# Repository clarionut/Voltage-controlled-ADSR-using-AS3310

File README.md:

# Voltage controlled ADSR using AS3310

This repository contains details of my modified version of the [Digisound 80-18 multifunction envelope generator]( http://www.digisound80.co.uk/digisound/modules/80-18.htm). I was particularly interested in its versatility with three operating modes
- normal (standard ADSR)
- automatic (gives a complete ADR cycle following a brief trigger input)
- damped (gives a piano-like envelope with initial attack and decay, but instead of a constant sustain while the gate is high the envelope continues to decay at a rate determined by the release setting, finally shutting off the envelope when the gate goes low)

Curiously, given that the 3310 chip is intrinsically voltage controlled, the Digisound 80-18 module only featured control of the envelope by potentiometers rather than allowing external CV control, although there are other designs (e.g. by [gerb-ster](https://github.com/gerb-ster/Curtis-VC-ADSR)) which do allow external control.

I'm absolutely delighted with this module and immediately built a second. I wouldn't want to be limited to a conventional ADSR having used this one.

## Issues
There is a known issue with the Digisound 80-18 module leading to repeated AD triggering with relatively weak gate inputs. The Digisound 80-18A documentation suggests using two gates from a CD40106 in series to condition the gate signal and [Eddy Bergman used a switch](https://www.eddybergman.com/2020/05/synthesizer-build-part-33-digisound-80.html) to break the loop responsible for multiple triggering. I chose to feed the gate input into an op-amp comparator so even rather low-level gates trigger the ADSR reliably.

Note that I have not encountered any of the odd behaviour in Automatic mode as described by Eddy Bergman, in my case this mode works exactly as described in the Digisound 80-18 documentation.

Running the circuit on a breadboard showed that with linear potentiometers much of the travel of the pot covered only very short time intervals, making the more useful longer times quite hard to adjust. This was easy to fix using fake C-taper pots (500k linear pot with a 100k resistor from the wiper to the +ve supply end of the pot).

## Additional features
I found that in Damped mode the final release was very rapid producing an audible click. Adding a 510R resistor between the AS3310 chip pin 13 and transistor TR2 (Digisound schematic) / Q2 (my schematic) gave a rapid release without clicking. In the end I added a 2k 'Release 2' pot to make this final release phase manually adjustable.

Coincidentally, at the time I was working on this circuit I was also fixing an issue with the envelope generator of the filter in my Formanta Polivoks. This has an autorepeat mode, enabled by setting the envelope to AD mode and the sustain level to zero. It uses an op-amp comparator to generate an internal trigger signal when the envelope voltage falls below a threshold of a few mV. I included this feature in this ADSR, providing an 'end of envelope' output to trigger other events in the synth, and included a LOOP option on the mode switch allowing the module to run continously (essentially as an 'ADR LFO') in Automatic mode with frequencies up to about 120Hz.

The decay CV input is normalled to the attack input and the release input is normalled to decay, allowing flexibility in external CV control.

There are out-of-range monitor LEDs on the four CV inputs to warn if the combined potentiometer & external CV levels exceed the maximum useful control voltage (no damage would result, it simply wouldn't be effective).

## Repository contents
The schematics folder contains the full schematic as a PDF document, the PCB layout (with the front ground plane removed for clarity) and a subfolder containing the kicad 7 project. The kicad schematic and PCB use some custom symbols and footprints so you may have to download my custom [kiCad libraries](https://github.com/clarionut/kiCad_libraries). Note that the PCB layout is intended to be processed by the 'round tracks' kicad plugin as shown in the PCB.pdf document. The kicad project files only include the unprocessed .kicad_pcb file. I've also included the Gerbers (in the Gerbers folder!) of the rounded tracks PCB for direct fabrication in case they're useful for anyone.

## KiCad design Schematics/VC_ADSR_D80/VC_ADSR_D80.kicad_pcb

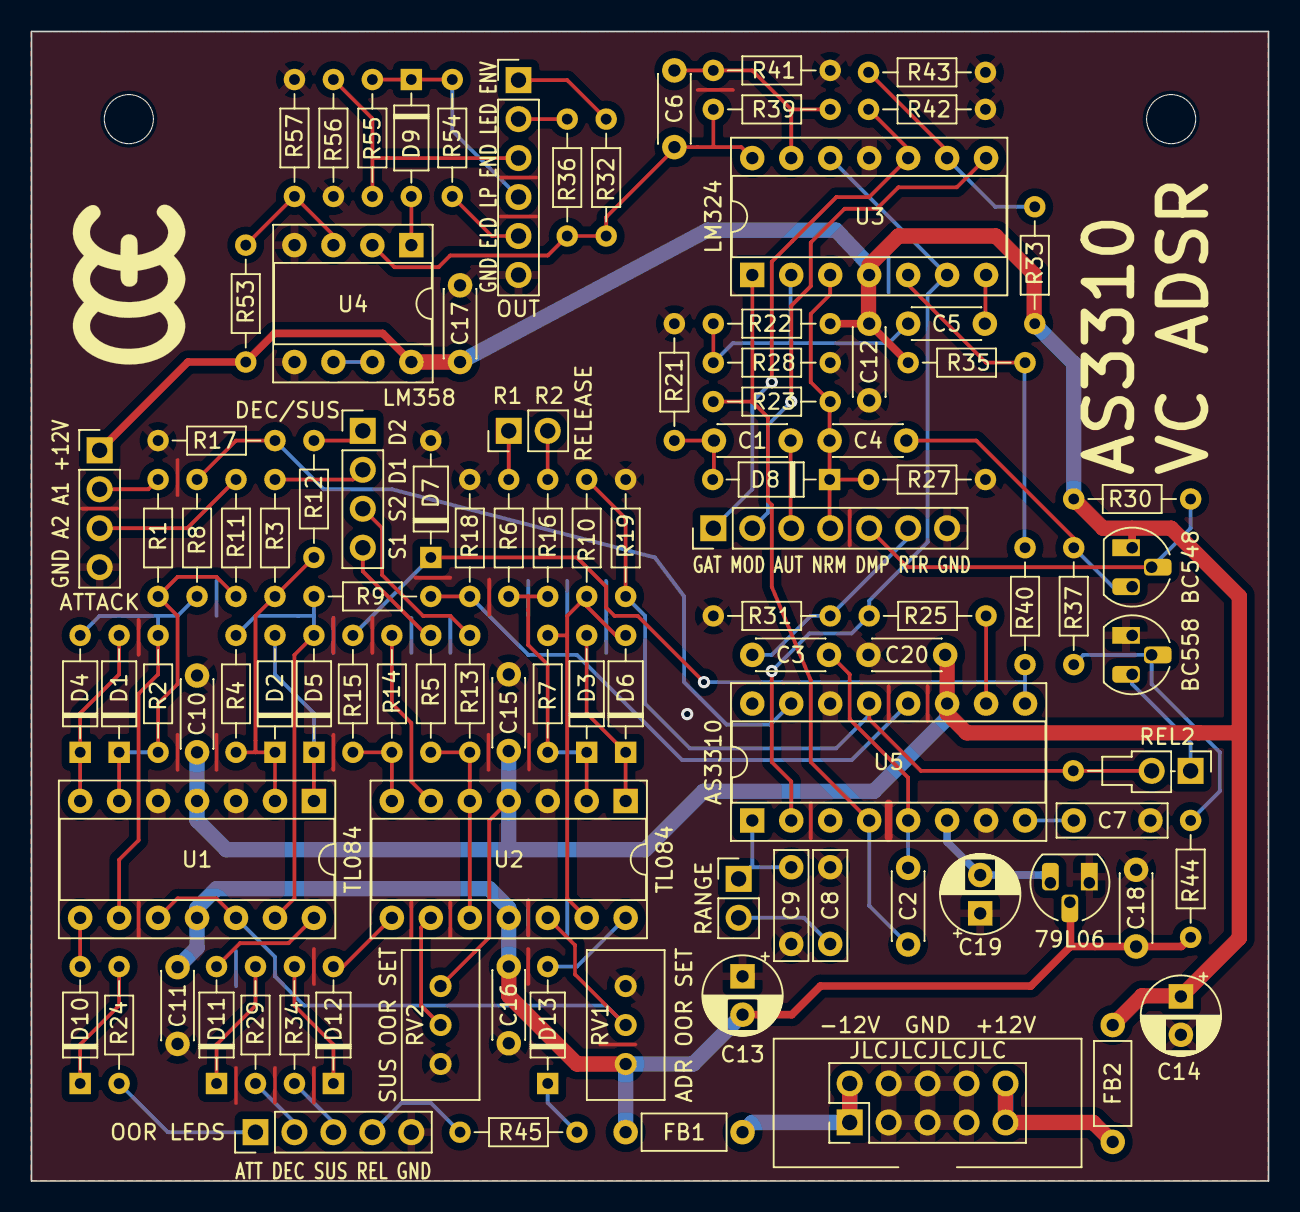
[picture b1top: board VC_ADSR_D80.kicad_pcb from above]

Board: 2 copper layers, 80.6 x 74.9 mm, 101 parts (0 on the bottom side), 75 nets.

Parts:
C1, C5: 33n; C_Disc_D4.3mm_W1.9mm_P5.00mm
C2: 3n3; C_Disc_D4.3mm_W1.9mm_P5.00mm
C3, C4: 10n; C_Disc_D4.3mm_W1.9mm_P5.00mm
C6: 22p; C_Disc_D4.3mm_W1.9mm_P5.00mm
C7: 4n7; C_Rect_L7.0mm_W2.0mm_P5.00mm
C8: 100n; C_Rect_L7.0mm_W2.0mm_P5.00mm
C9: 33n; C_Rect_L7.0mm_W2.0mm_P5.00mm
C10, C11, C12, C15, C16, C17, C20: 100n; C_Disc_D4.3mm_W1.9mm_P5.00mm
C13, C14: 10u; CP_Radial_D5.0mm_P2.50mm
C18: 330n; C_Disc_D4.3mm_W1.9mm_P5.00mm
C19: 1u; CP_Radial_D5.0mm_P2.50mm
D1, D2, D3, D4, D5, D6, D9, D10, D11, D12, D13: 1N914; D_DO-35_SOD27_P7.62mm_Horizontal
D7: 5V1; D_DO-35_SOD27_P7.62mm_Horizontal
D8: BAT43; D_DO-35_SOD27_P7.62mm_Horizontal
FB1, FB2: FB; L_Axial_L5.3mm_D2.2mm_P7.62mm_Horizontal_Vishay_IM-1
J1: ATTACK; PinHeader_1x04_P2.54mm_Vertical
J2: DECAY/SUSTAIN; PinHeader_1x04_P2.54mm_Vertical
J3: RELEASE; PinHeader_1x02_P2.54mm_Vertical
J4: GATE/TRG; PinHeader_1x07_P2.54mm_Vertical
J5: OOR_LEDS; PinHeader_1x05_P2.54mm_Vertical
J6: OUT; PinHeader_1x06_P2.54mm_Vertical
J7: REL.2; Resistor_Header
J8: RANGE; PinHeader_1x02_P2.54mm_Vertical
J9: POWER; Power_2x05
Q1: BC548; TO-92_HandSolder
Q2: BC558; TO-92_HandSolder
R1, R3, R5, R6, R11, R12, R13, R14, R16, R22, R30, R31, R33, R39, R41: 100k; R_Axial_DIN0204_L3.6mm_D1.6mm_P7.62mm_Horizontal
R2, R4, R7: 51k; R_Axial_DIN0204_L3.6mm_D1.6mm_P7.62mm_Horizontal
R8, R9, R10, R24, R29, R34, R45: 20k; R_Axial_DIN0204_L3.6mm_D1.6mm_P7.62mm_Horizontal
R15, R56: 39k; R_Axial_DIN0204_L3.6mm_D1.6mm_P7.62mm_Horizontal
R17, R18, R19, R32: 1k; R_Axial_DIN0204_L3.6mm_D1.6mm_P7.62mm_Horizontal
R21, R23, R36, R40, R43, R54: 10k; R_Axial_DIN0204_L3.6mm_D1.6mm_P7.62mm_Horizontal
R25, R28, R55: 22k; R_Axial_DIN0204_L3.6mm_D1.6mm_P7.62mm_Horizontal
R27: 6k8; R_Axial_DIN0204_L3.6mm_D1.6mm_P7.62mm_Horizontal
R35: 10M; R_Axial_DIN0204_L3.6mm_D1.6mm_P7.62mm_Horizontal
R37: 47k; R_Axial_DIN0204_L3.6mm_D1.6mm_P7.62mm_Horizontal
R42: 470k; R_Axial_DIN0204_L3.6mm_D1.6mm_P7.62mm_Horizontal
R44: 150k; R_Axial_DIN0204_L3.6mm_D1.6mm_P7.62mm_Horizontal
R53: 1M; R_Axial_DIN0204_L3.6mm_D1.6mm_P7.62mm_Horizontal
R57: 680R; R_Axial_DIN0204_L3.6mm_D1.6mm_P7.62mm_Horizontal
RV1, RV2: 500k; Potentiometer_Bourns_3296W_Vertical
U1, U2: TL084; DIP-14_W7.62mm_Socket
U3: LM324; DIP-14_W7.62mm_Socket
U4: LM358; DIP-8_W7.62mm_Socket
U5: AS3310; DIP-16_W7.62mm_Socket
U6: LM79L06; TO-92_HandSolder

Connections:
+12V: C10.1, C12.1, C14.1, C15.1, C17.1, C20.1, FB2.1, J1.1, Q1.1 (C), R22.2, R30.1, R33.2, R35.2, R53.2, RV2.1, U1.4 (V+), U2.4 (V+), U3.4 (V+), U4.8 (V+), U5.11 (VCC)
-6V: C19.2, U5.6 (VEE), U6.3 (VO)
-12V: C11.1, C13.2, C16.1, C18.1, FB1.1, R44.1, RV1.3, U1.11 (V-), U2.11 (V-), U6.2 (VI)
A: R8.2, R17.2, U5.15 (VCA)
AM: D4.2 (A), R2.2, R8.1, U1.9 (-)
ATT1: J1.2, R1.1
ATT2: J1.3, R11.1
AUTO: C1.1, J4.3
D: R9.2, R18.2, U5.12 (VCD)
DAMP: J4.5, Q1.2 (B), R30.2
DEC1: J2.2, R3.1
DEC2: J2.1, R12.1
DM: D5.2 (A), R4.2, R9.1, U1.13 (-)
END: J6.3, R55.2, R56.2
ENDLD: J6.5, R54.2
G: C2.1, R23.2, U3.1, U5.4 (GATE)
GATE: J4.1, R42.2, U3.10 (+)
GND: C7.2, C8.2, C9.2, C10.2, C11.2, C12.2, C13.1, C14.2, C15.2, C16.2, C17.2, C18.2, C19.1, C20.2, D7.2 (A), J1.4, J4.7, J5.5, J6.6, J9.3, J9.4, J9.5, J9.6, J9.7, J9.8, Q2.1 (C), R17.1, R18.1, R19.1, R21.1, R27.1, R28.1, R31.1, R41.1, R42.1, R43.1, R56.1, R57.1, RV1.1, RV2.3, U1.3 (+), U1.5 (+), U2.3 (+), U3.11 (V-), U4.4 (V-), U4.5 (+), U5.7 (PGND), U5.14 (GND), U6.1 (GND)
LED: J6.2, R36.2
LOOP: D9.1 (K), J6.4, R54.1, R55.1
MODE: J4.2, U3.8
NORM: C4.1, D8.1 (K), J4.4, R23.1, R27.2, U3.3 (+)
unnamed: C5.2, U3.7
unnamed: D1.2 (A), D4.1 (K), U1.7
unnamed: D1.1 (K), R1.2, R2.1, R11.2, U1.6 (-)
unnamed: D2.2 (A), D5.1 (K), U1.1
unnamed: D2.1 (K), R3.2, R4.1, R12.2, U1.2 (-)
unnamed: D3.2 (A), D6.1 (K), U2.1
unnamed: D3.1 (K), R6.2, R7.1, R16.2, U2.2 (-)
unnamed: C1.2, D8.2 (A), R21.2
unnamed: D9.2 (A), U4.1
unnamed: D10.2 (A), U1.8
unnamed: D10.1 (K), R24.1
unnamed: D11.2 (A), U1.14
unnamed: D11.1 (K), R29.1
unnamed: D12.2 (A), U2.8
unnamed: D12.1 (K), R34.1
unnamed: D13.2 (A), U2.14
unnamed: D13.1 (K), R45.1
unnamed: FB1.2, J9.1, J9.2
unnamed: FB2.2, J9.9, J9.10
unnamed: C4.2, Q1.3 (E), R37.2
unnamed: Q2.2 (B), R37.1, R44.2
unnamed: R14.2, R15.1, U2.7
unnamed: RV1.2, U1.10 (+), U1.12 (+), U2.12 (+)
unnamed: R14.1, U2.6 (-)
unnamed: RV2.2, U2.9 (-)
unnamed: C5.1, R22.1, R28.2, U3.2 (-)
unnamed: R35.1, R40.2, U3.5 (+)
unnamed: R25.1, U3.6 (-), U3.12 (+), U5.2 (ENVOUT)
unnamed: R33.1, R43.2, U3.9 (-)
unnamed: C6.1, R39.1, R41.2, U3.13 (-)
unnamed: R53.1, R57.2, U4.3 (+)
unnamed: C6.2, R32.1, R36.1, R39.2, U3.14, U4.2 (-)
unnamed: U4.6 (-), U4.7
unnamed: C7.1, U5.8 (CCOMP)
unnamed: R25.2, U5.10 (IIN)
OORA: J5.1, R24.2
OORD: J5.2, R29.2
OORR: J5.4, R45.2
OORS: J5.3, R34.2
OUT: J6.1, R32.2
R: J7.2, R10.2, R19.2, U5.13 (VCR)
R2: J7.1, Q2.3 (E)
REL1: J3.1, R6.1
REL2: J3.2, R16.1
RETRIG: C3.1, J4.6, R31.2
RM: D6.2 (A), R7.2, R10.1, U2.13 (-)
RNG1: C9.1, J8.1, U5.1 (CAP)
RNG2: C8.1, J8.2
S: D7.1 (K), R15.2, R40.1, U5.9 (VCS)
SM: R5.2, R13.2, U2.5 (+), U2.10 (+)
SUS1: J2.4, R5.1
SUS2: J2.3, R13.1
T: C2.2, C3.2, U5.5 (TRIG)

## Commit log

2025-08-27 Create README.md
    A voltage controlled ADSR based on the AS3310 chip
2025-08-30 Create tmp
